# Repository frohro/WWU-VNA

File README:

This is some source code for the WWU VNA.  The hardware files can be found at this repository:  
https://github.com/frohro/WWU-VNA

These instructions were done an a Ubuntu Linux computer.  They will vary slightly for Windows or OS X.

Build Instructions:

	- git clone the repository.  
	- Install Code Composer Studio. (This works with CCS 8.2 and 9.0.) 
		- You need the MSP432 Red board library version 5.23.1 or later or you will have build errors.
	- Install Energia, and using Energia's Tools->Boards:->Boards Manager, add the MSP432P401P (red board)
	- Energia uses the Arduino way of handling libraries, and it is easiest to use that as well, because
		CCS knows how to import things better that way.  So in your ~/Energia/libraries folder make 
		folders for each of the libraries.  Mine look like this.
		:~/Energia$ ls -lah libraries
		total 36K
		drwxr-xr-x 8 frohro frohro 4.0K Apr 15 21:07 .
		drwxr-xr-x 5 frohro frohro 4.0K Apr  5 14:30 ..
		drwxr-xr-x 2 frohro frohro 4.0K Apr 21 21:29 adc14vna
		drwxr-xr-x 2 frohro frohro 4.0K Apr 15 21:15 constants
		drwxr-xr-x 2 frohro frohro 4.0K Apr  5 14:33 DynamicCommandParser
		-rw-r--r-- 1 frohro frohro   88 Oct 11  2018 readme.txt
		drwxr-xr-x 2 frohro frohro 4.0K Apr 21 21:31 si5351
		drwxr-xr-x 2 frohro frohro 4.0K Apr 21 21:30 SignalProcessing
		
		Inside those make symbolic links to the appropriate files in your git repository.
		For example, 

	- Import Energia Sketch using File->Import...->Energia->Energia Sketch.
	- Be sure to select MSP432P401R as the processor.
	- Right click on the project, and select add files.
		- Add the .cpp, .c, and .h files.
	- Click the hammer to build in CCS.

	- Under languages, select C11 and c++17
	- Under Build Settings->Miscellaneous->Miscellaneous C++ source specific flags add -fpermissive.

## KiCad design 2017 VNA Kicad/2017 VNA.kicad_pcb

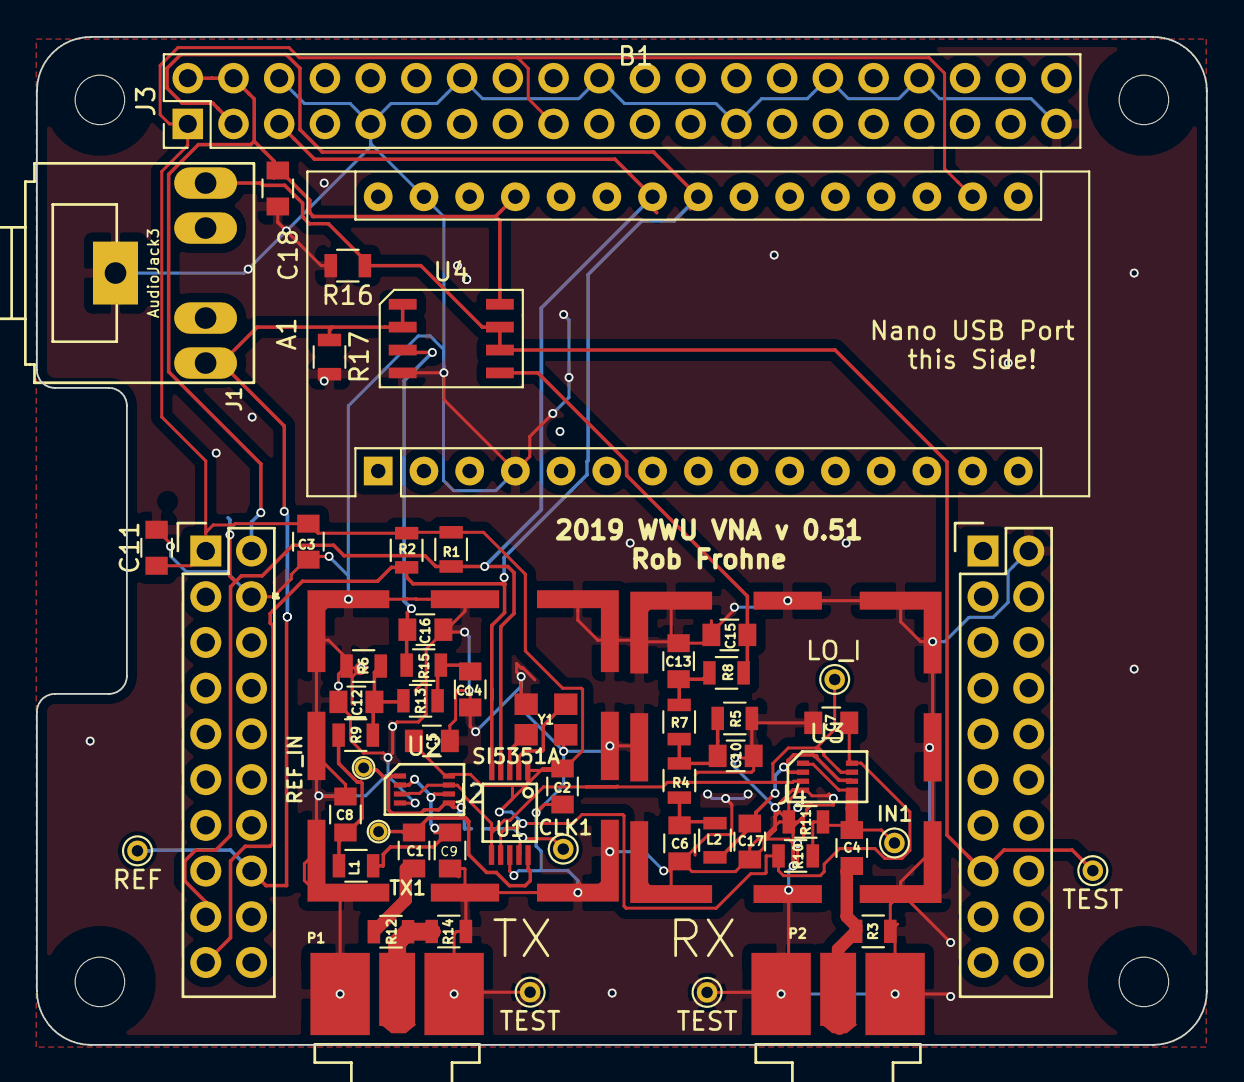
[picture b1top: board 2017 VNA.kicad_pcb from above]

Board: 2 copper layers, 65.0 x 56.0 mm, 60 parts (1 on the bottom side), 27 nets.

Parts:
A1: Arduino_Nano_v3.x; Arduino_Nano
B1: EXP-_MSP432P401R_BoosterPack; TI_BoosterPack
C1, C4: 1.0uF; C_0805
C2: .1uf; C_0805
C3: 10uF; C_0805
C5, C7: .1uF; C_0805
C6, C8: 680nF; C_0805
C9, C17: .005uF; C_0805
C10, C12: 10nF; C_0805
C11, C18: 0.1uF; C_0805
C13, C14, C15, C16: 1nF; C_0805
CLK1: LO_Q; PINTST
GND1, GND2: TEST; PINTST
IN1: IN; PINTST
J1: AudioJack3; Tayda_3.5mm_stereo_TRS_jack_A-853
J2, J4: RF_Shield_Two_Pieces; LAIRD-BMI-S-202
J3: Raspberry_Pi_2_3; Pin_Header_Straight_2x20_Pitch2.54mm
JP1: Jumper; SOLDER_JUMPER
L1, L2: 100uH; L_0805
LO_I1: LO_I; PINTST
P1: Output; SMA_EDGE
P2: Input; SMA_EDGE
R1, R2: 4.7k; R_0805
R3: 47; R_0805
R4, R9: 10k; R_0805
R5, R6: 30k; R_0805
R7, R13: 51k; R_0805
R8, R15: 1M; R_0805
R10: 39K; R_0805
R11: 220K; R_0805
R12, R14: R; R_0805
R16, R17: 180; R_0805
TP1: REF_IN; PINTST
TP2: REF; PINTST
TP3: TEST; PINTST
TX1: LO_Q; PINTST
U1: SI5351A; MSOP-10
U2, U3: NL7WB66; VFSOP-8
U4: LM2904; SOIC-8
Y1: CX3225

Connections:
+3V3: A1.17, B1.3.3V, C2.2, C3.1, C5.2, C7.1, C11.1, J3.1, J3.17, R1.2, R2.2, R10.1, U1.1, U1.7, U2.8, U3.8
+5V: A1.27, B1.5V, C18.1, J3.2, J3.4, U4.8
/LO_I: LO_I1.1, U1.6, U2.3, U2.7, U3.3, U3.7
/Ref_In: JP1.2, TP1.1, U2.1, U2.5
/SCL: A1.24, B1.P6.5, J3.5, R1.1, U1.4
/SDA: A1.23, B1.P6.4, J3.3, R2.1, U1.5
/TX: C1.2, TX1.1, U1.10
/Test_In: C4.1, IN1.1, R10.2, R11.1, U3.1, U3.5
GND: A1.4, A1.29, B1.GND, B1.GND1, C2.1, C3.2, C5.1, C6.2, C7.2, C8.2, C9.2, C10.2, C11.2, C12.2, C13.2, C14.2, C15.2, C16.2, C17.2, C18.2, GND1.1, GND2.1, J1.1, J2.1, J3.6, J3.9, J3.14, J3.20, J3.25, J3.30, J3.34, J3.39, J4.1, P1.2, P2.2, R3.2, R5.2, R6.2, R11.2, R14.1, R16.2, R17.2, U1.8, U2.4, U3.4, U4.4, Y1.2, Y1.4
unnamed: B1.P4.7, J1.3, R17.1, TP2.1, U4.1, U4.2
unnamed: B1.P5.1, J1.2, R16.1, TP3.1, U4.6, U4.7
unnamed: C1.1, R12.2
unnamed: C4.2, P2.1, R3.1
unnamed: C6.1, L2.2, R4.2
unnamed: C8.1, L1.2, R9.2
unnamed: C9.1, L1.1, U2.2, U2.6
unnamed: C10.1, R4.1, R5.1, R7.2
unnamed: C12.1, R6.1, R9.1, R13.2
unnamed: C13.1, R7.1, R8.2
unnamed: C14.1, R13.1, R15.2
unnamed: C15.1, R8.1, U4.5
unnamed: C16.1, R15.1, U4.3
unnamed: C17.1, L2.1, U3.2, U3.6
unnamed: CLK1.1, JP1.1, U1.9
unnamed: P1.1, R12.1, R14.2
unnamed: U1.2, Y1.1
unnamed: U1.3, Y1.3

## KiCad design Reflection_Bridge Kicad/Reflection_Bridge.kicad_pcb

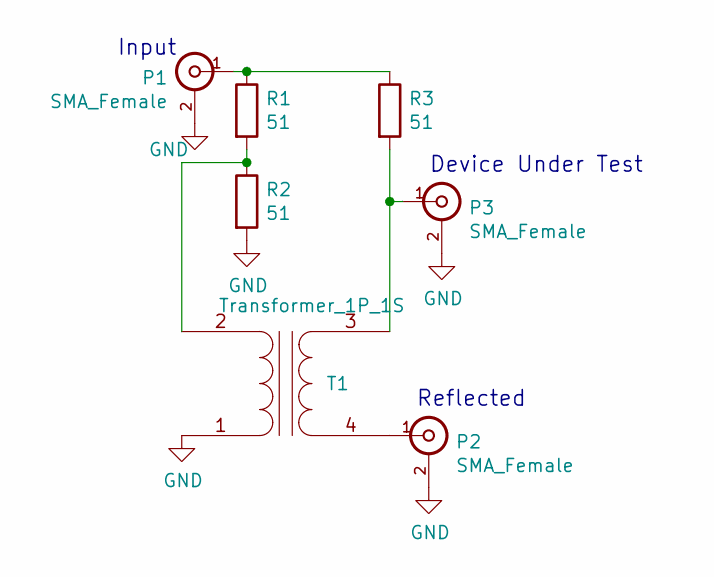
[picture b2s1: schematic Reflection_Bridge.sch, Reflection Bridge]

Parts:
P1, P2, P3: SMA_Female; SMA_EDGE
R1, R2, R3: 51; R_0805
T1: Transformer_1P_1S; 1_to_1_Balun

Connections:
GND: P1.2 (Ext), P2.2 (Ext), P3.2 (Ext), R2.2, T1.1 (AA)
unnamed: P1.1 (In), R1.1, R3.1
unnamed: P2.1 (In), T1.4 (SB)
unnamed: P3.1 (In), R3.2, T1.3 (SA)
unnamed: R1.2, R2.1, T1.2 (AB)

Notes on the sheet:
Input
Device Under Test
Reflected

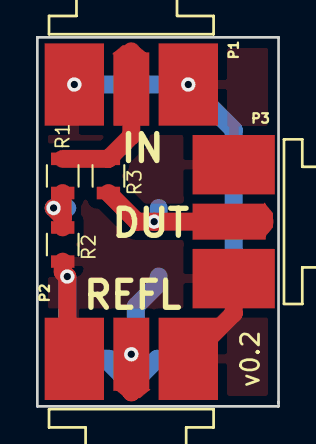
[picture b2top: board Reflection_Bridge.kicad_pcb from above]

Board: 2 copper layers, 13.4 x 20.5 mm, 7 parts (1 on the bottom side), 5 nets.

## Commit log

2017-05-23 reinitialized files
2017-05-24 Bug fixes to serial code and "TIME" command added.
2017-12-31 Updating to work with the latest PCB (version 0.3).
2018-04-02 Initial Commit
    I am starting a repository for the WWU Vector Network Analyzer generally. In the past, I have shared software on github, but this will have the hardware design files as well as the software.
2018-04-03 fixed library files
2018-04-03 sym-lib-table is necessary
2018-04-03 added some files that are needed
2018-04-03 more libraries that are needed
2018-04-03 fixed some test point libraries
2018-04-03 Added note about R3.
    R3 added after PCB was manufactured.
2018-04-03 fixed a few more lib values
2018-04-03 added note on R3 (added after PCB made)
2018-04-03 Added CCS
2018-04-03 Modified to work with the 2018 Simple VNA version 0.4 in Kicad.
2018-04-03 This directory contains code to test in a simple way the Si5351a portion of the VNA.
2018-04-03 Octave files for communicating with VNA
2018-04-03 Added LTSpice Simulations
2018-04-04 Update .gitignore to not keep Debug*
2018-04-04 We don't need the build directories.
2018-04-04 Deleting build files.
2018-04-04 Added reflection bridge hardware design files
2018-04-10 Updated includes to work with Code Composer Studio version 8.
2018-04-15 For plotting Smith Charts and associated S parameters.
2018-04-16 octave necessities
2018-04-16 added gitignore for Release directory and deleted a ; where it didn't need to be.
2018-04-16 Fixed a bug in sending refSum and measSum.
2018-04-16 Add the correct octave test scripts.
2018-04-16 Got rid of Hanning window. Fixed internal H(f) calculations. Changed octave files for better testing.
2018-04-17 updated the LTSpice files and fixed a bug with C12 (wrong value).
2018-04-18 Fixed a few bugs.... The measurements don't seem repeatable though.
2018-04-18 Updated the Si5351a library, and calibrated my oscillator.
2018-04-18 Frequency was 1/100 of what I wanted. Now it is correct is setOscillator.
2018-04-18 Revert "Frequency was 1/100 of what I wanted. Now it is correct is"
    This reverts commit e89e7d64f5e505ba8f0312610786470331df18ac.
2018-04-18 Undo fix in case it blows oscillators.
2018-04-19 Fixed the si5351a library prblem by using 2.0.6, and changing the set_correction function to one argument. Octave starts indexing at 1 instead of 0, so fixed that. Fixed the bug in octave script that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
2018-04-23 Start on some python scrips
2018-04-23 Fix statistics calulations
2018-04-24 Fix some printing errors, and change phase to be in degrees. Also add a custom frequency entering.
2018-04-24 Make some statistics calulation optimizations, and hopefully fix a bug on linux where it doesn't like file paths starting with a '/'. Also allow for non-integer frequencies in MHz for better frequenc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
2018-04-25 Go back to getting the sample frequency from the board.
2018-04-26 New filter idea in progress, and a needed .gitignore for LTSpice-Simulations folder
2018-04-26 Make the new filter realistic
2018-04-26 Improvements to the new filter.
2018-04-27 Did some more work on the LPF.
2018-04-27 Make the python script automatically write to a file, also add a folder for all of the measurements.
2018-04-27 Make PEP8 conformant, and modify script header.
2018-04-28 added dakiry's low pass filter design without inductor
2018-04-30 Simulation with the new LPF including the .1mH inductor.
2018-04-30 Forgot to hit ctrl-s.
2018-05-07 Fix this gitignore to exclude everything except for what we want.
2018-05-07 Make python script more general.
2018-05-25 Put all of the filtering components on top
2018-05-28 Added Ferrit beads to input and output of ADC
2018-05-28 Fixed version number and orientation of component labels
2018-05-29 Fixed the master branch with the emblem and test libs.
2018-05-29 Actually changed the version number this time. Filled in ground planes and other cosmetic issues.
2018-05-29 Fixed the GND label.
2018-05-29 A little clean up of the title blocks, schematic, etc.
2018-05-29 Our board changes
2018-05-29 A little clean up of the title blocks, etc.
2018-05-29 Trying this again
2018-05-29 Fix all DRC errors
2018-05-29 Hopefully ready for printing now
2018-05-29 Noticed I didn't save. This incorporates those saved changes.
2018-06-05 Changet the IF to 155 Hz, and the octave script serial_test_time.m to match.
2018-06-05 Added two more window functions for testing
2018-06-08 Revert testime.py because it got broken. Also ignore measurements while device is getting to steady state.
2018-06-08 Add hanning window in the python script and make the harmonics print out again in the serial_test_time script
2018-06-10 Updated project Readme.md with names
2018-06-10 Updated readme with our project documentation
2018-06-10 Changed to blackman window function
2018-06-10 Consolidated changes from other branch to this branch
2018-06-10 small correction
2018-06-10 small corrections
2018-06-10 Modify python script to include standard deviations of the raw reference and measured values, imaginary, real, and magnitude.
2018-06-11 Put the Hanning window back in and got rid of the memory optimization.
2018-06-11 Active LPF w/ Cutoff Frequency 1021 Hz
2018-06-11 Hurray... DMA....
2018-06-11 Implement variable sided buffer lengths using Ping Pong mode on the DMA module.
2018-06-11 Committed the wrong things. Oh well. No longer ignoring the first five measurements.
2018-06-19 New Images
2018-09-06 Added interactive BOM.
2018-11-29 Added the sound card testing python script.
2018-12-06 A couple of optimizations, also skip the first 2 DMA ping pong result buffers as something weird happens on the first and possibly second flip, doing this yields vastly better results. Also plot a fe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
2018-12-06 Adding to README for CCSv8.2, and making compatible with Kicad v5.
2018-12-07 A whole lot of things working now - Update to CCS 8.2 - fix DMA to get rid of inflection at beginning - compute the first harmonic on the board and send it back with the COMPUTE command. - Create FIR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
2018-12-09 The commit that fixes everything.
    - Found bug in python script where wrong size hanning window was generated
    - What do you get when you cross an idiot with a small math mistake? 6 months of wondering what the problem was.
    - Added script to compare math being done on board to a library that we have some faith in.
    - Added minus sign to the imaginary filter part becuase I forgot it becuase I'm an idiot.
2018-12-09 Don't think that minus sign is supposed to be there...
2018-12-10 Images for GUI Documentation
2018-12-10 dis is reverse order quick hotfix
2018-12-10 Start on making a cool GUI work
2018-12-16 Added important info to the README aout necessities for building.
2018-12-16 Refactored the computeFundamental() out, and modified sweepFreqMeas().
2018-12-17 Fixed up serial_test.m to work with the new format.
2018-12-17 Fixed sign error in SignalProcessing again, and changed plot in TestTime.py.
2018-12-17 Fix the sampling frequency to be F_IF lower than F.
2018-12-18 Optimized delay on setOscillator().
2018-12-18 These delays make it stable for f<100MHz.
2018-12-18 Increased the drive to 8mA again.
2018-12-19 Added through cal octave script.
2018-12-19 Added Octave scripts to measure the reflection (with SOL cal).
2018-12-20 Adding cal and GUi to octave code.
2018-12-20 Added a bit of GUI stuff to the vna_through_cal.m
2018-12-20 Refactored the GUI a bit, and added more tweaks.
2018-12-20 Added isolation calibration. It improved isolation 20-30 dB.
2018-12-20 Added the option to do more sweeps with this cal set.
2018-12-20 Added some more error handling.
2018-12-21 Added a few more cal testing options.
2019-01-07 Push up quantization noise simulator python script
2019-02-11 version 5 hardware design (more isolation between channels)
2019-02-12 Cosmetic cleanup.
2019-02-21 Moved pin assignments for v 0.5.
2019-03-20 Making sure it is up to date.
2019-04-24 Some changes to the Octave directory.
2019-04-24 Added the bom for the reflection bridge.
2019-04-29 Got rid of quadrature.h
2019-04-29 This is a little more stable (I think). We changed to a println.
2019-04-29 Removed unused DSP routine.
2019-04-30 Added fix me notes to Reflection Bridge!
2019-04-30 Added the BOM
2019-04-30 Added notes to fix T1 footprint on the reflection bridge.
2019-05-03 Fixed the annoying bug where the VNA would go picking flowers....
2019-05-03 Enhanced octave scripts and fixed bug where VNA goes picking daisies.
2019-05-05 Fixed the TIME command.
2019-05-05 Made TIME work.
2019-05-06 Working on fixing the isolation.
2019-05-07 Added octave script to use soundcard.
2019-05-08 Cleaned up comments in adc14vna.cpp
2019-05-09 Made the serial port more automatic in octave.
2019-05-09 Added some test octave scripts, and improved others.
2019-05-09 Added some test octave scripts & improved serial port choosing in others.
2019-05-10 Fixed things for TaNek
2019-05-10 Added instruction to change the sample and hold timer for testing.
2019-05-15 New PCB spin.
2019-05-15 fixing things.
2019-05-15 Added the buffer stage and ADC for MSP432 it the LTspice simulation.
2019-05-15 Improved NL7WB66 model.
2019-05-16 Fixed the reflection bridge, and some bugs in octave scripts.
2019-05-16 Added v0.2 of reflection bridge.
2019-05-16 Added the footprint for the 3.5mm connector.
2019-05-17 Added v0.51 to the Kicad directory.
2019-05-20 Hwi interrupt header testing....
2019-06-03 updated the pcb...
2019-06-04 Added some arduino python test scripts.
2019-06-07 Added 180 ohms to bias the emitter follower on the LM2094.
2019-06-07 Updated the netlest and PCB for v0.52 (180 ohm current sink).
2019-06-08 Changed the spice model to match more what was built in v0.5.
2019-06-10 Added vna2019.asc to the LTspice simulations.
